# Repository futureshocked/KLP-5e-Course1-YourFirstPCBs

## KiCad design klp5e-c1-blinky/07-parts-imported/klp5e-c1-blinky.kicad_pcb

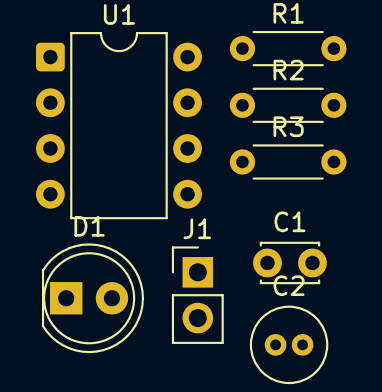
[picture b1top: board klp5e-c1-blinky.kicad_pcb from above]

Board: 2 copper layers, 8 parts (0 on the bottom side), 7 nets, no tracks yet.

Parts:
C1: 10 nF; C_Disc_D3.0mm_W2.0mm_P2.50mm
C2: 10 uF; C_Radial_D4.0mm_H5.0mm_P1.50mm
D1: LED; LED_D5.0mm
J1: Conn_01x02_Pin; PinHeader_1x02_P2.54mm_Vertical
R1: 10 k; R_Axial_DIN0204_L3.6mm_D1.6mm_P5.08mm_Horizontal
R2: 47 k; R_Axial_DIN0204_L3.6mm_D1.6mm_P5.08mm_Horizontal
R3: 470; R_Axial_DIN0204_L3.6mm_D1.6mm_P5.08mm_Horizontal
U1: NE555P; DIP-8_W7.62mm

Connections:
/BLINK: D1.2 (A), U1.3 (OUT)
/DISCH: R1.2, R2.1, U1.7 (DISCH)
/TIMING: C2.1, R2.2, U1.2 (TRIG), U1.6 (THRES)
GND: C1.2, C2.2, J1.1, R3.2, U1.1 (GND)
unnamed: D1.1 (K), R3.1
unnamed: C1.1, U1.5 (CONT)
VCC: J1.2, R1.1, U1.4 (~RST), U1.8 (VCC)

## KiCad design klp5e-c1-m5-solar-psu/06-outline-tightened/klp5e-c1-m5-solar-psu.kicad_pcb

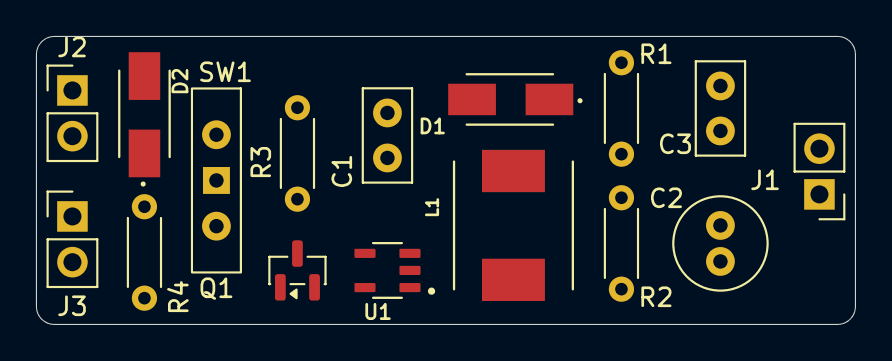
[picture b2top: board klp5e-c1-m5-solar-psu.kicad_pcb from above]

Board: 2 copper layers, 45.5 x 16.0 mm, 16 parts (0 on the bottom side), 8 nets, no tracks yet.

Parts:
C1: 4.7 uF, 50 V, X7R; C_Disc_D5.0mm_W2.5mm_P2.50mm
C2: 22 uF, 10 V, X7R; C_Radial_D5.0mm_H11.0mm_P2.00mm
C3: 10 pF, 50 V, X7R; C_Disc_D5.0mm_W2.5mm_P2.50mm
D1, D2: SS14; SMA
J1, J2, J3: Conn_01x02_Pin; PinHeader_1x02_P2.54mm_Vertical
L1: 10 uH, 680 mA; IND_ASPI-0630LR-100M-T15
Q1: 2N7002; SOT-23
R1, R4: 1 M; R_Axial_DIN0204_L3.6mm_D1.6mm_P5.08mm_Horizontal
R2: 604 k, 1%; R_Axial_DIN0204_L3.6mm_D1.6mm_P5.08mm_Horizontal
R3: 10 k; R_Axial_DIN0204_L3.6mm_D1.6mm_P5.08mm_Horizontal
SW1: SW_Wuerth; SW_Slide-03_Wuerth-WS-SLTV_10x2.5x6.4_P2.54mm
U1: AP3015AKTR-G1; SOT95P280X145-5N

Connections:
/BAT_P: D2.P2, J2.2, SW1.1 (B)
/OUT_P: C2.1, C3.1, D1.P2, J1.2, R1.1
/SOLAR_P: D2.P1, J3.1, Q1.1 (G), R4.1
GND: C1.2, C2.2, J1.1, J2.1, J3.2, Q1.2 (S), R2.2, R4.2, SW1.3 (A), U1.2 (GND)
unnamed: Q1.3 (D), R3.2, U1.4 (~SHDN)
unnamed: C1.1, L1.1, R3.1, SW1.2 (C), U1.5 (VIN)
unnamed: C3.2, R1.2, R2.1, U1.3 (FB)
unnamed: D1.P1, L1.2, U1.1 (SW)
